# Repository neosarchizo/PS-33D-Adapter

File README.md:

# PS-33D-Adapter
[Blue Sky] PS-33D (KiCad)

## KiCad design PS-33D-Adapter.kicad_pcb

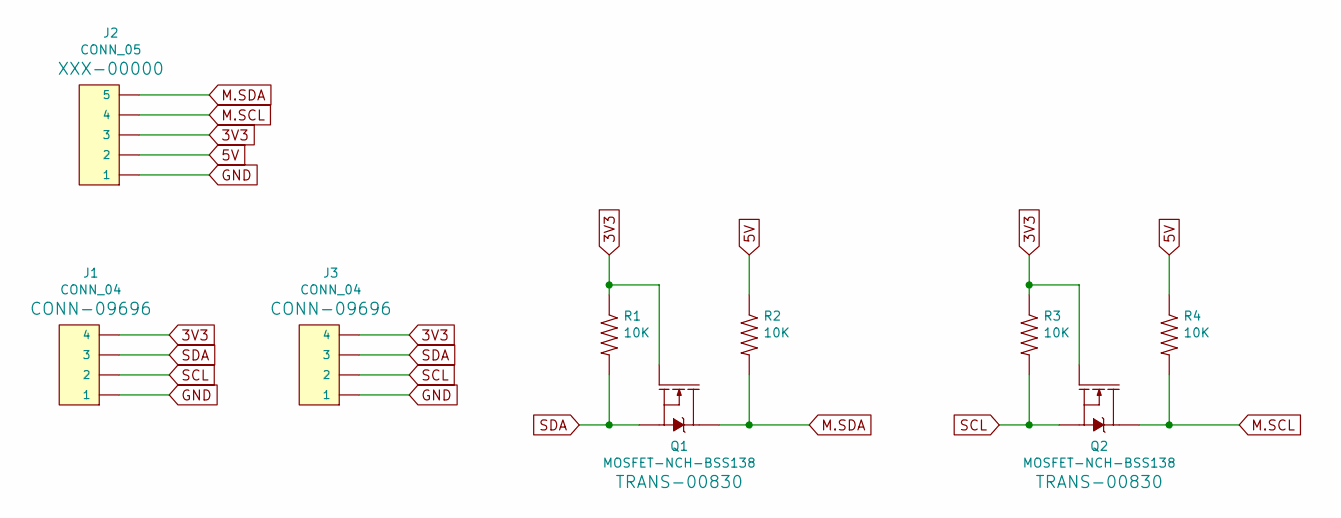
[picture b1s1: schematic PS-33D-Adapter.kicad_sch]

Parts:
J1, J3: CONN_04; PinHeader_1x04_P2.54mm_Vertical
J2: CONN_05; PinHeader_1x05_P2.54mm_Vertical
Q1, Q2: MOSFET-NCH-BSS138; SOT23-3
R1, R2, R3, R4: 10K; 0603

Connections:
3V3: J1.4, J2.3, J3.4, Q1.1 (G), Q2.1 (G), R1.1, R3.1
5V: J2.2, R2.1, R4.1
GND: J1.1, J2.1, J3.1
M.SCL: J2.4, Q2.3 (D), R4.2
M.SDA: J2.5, Q1.3 (D), R2.2
SCL: J1.2, J3.2, Q2.2 (S), R3.2
SDA: J1.3, J3.3, Q1.2 (S), R1.2

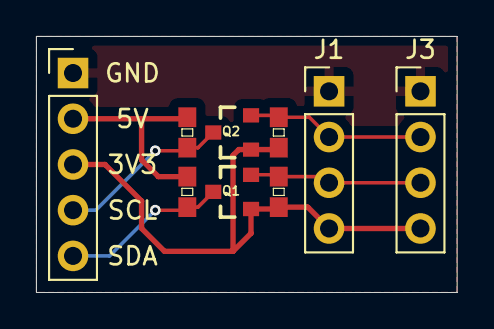
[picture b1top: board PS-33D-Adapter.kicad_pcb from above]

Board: 2 copper layers, 23.4 x 14.2 mm, 9 parts (0 on the bottom side), 7 nets.

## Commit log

2021-12-03 feat: add initial KiCad files
2021-12-08 feat: update netlist
2021-12-11 feat: update pcb
2021-12-13 feat: update mask clearance, mask min width
2021-12-14 feat: update setup
2021-12-18 feat: arrange parts
2021-12-21 feat: update schematic, pcb
2021-12-23 feat: add copper pour
2021-12-26 feat: update .gitignore
2022-01-04 feat: update footprints of connectors
2022-01-05 feat: remove all traces
2022-01-06 feat: add edge cut
2022-04-18 feat: update something
2022-05-12 chore: update .gitignore
